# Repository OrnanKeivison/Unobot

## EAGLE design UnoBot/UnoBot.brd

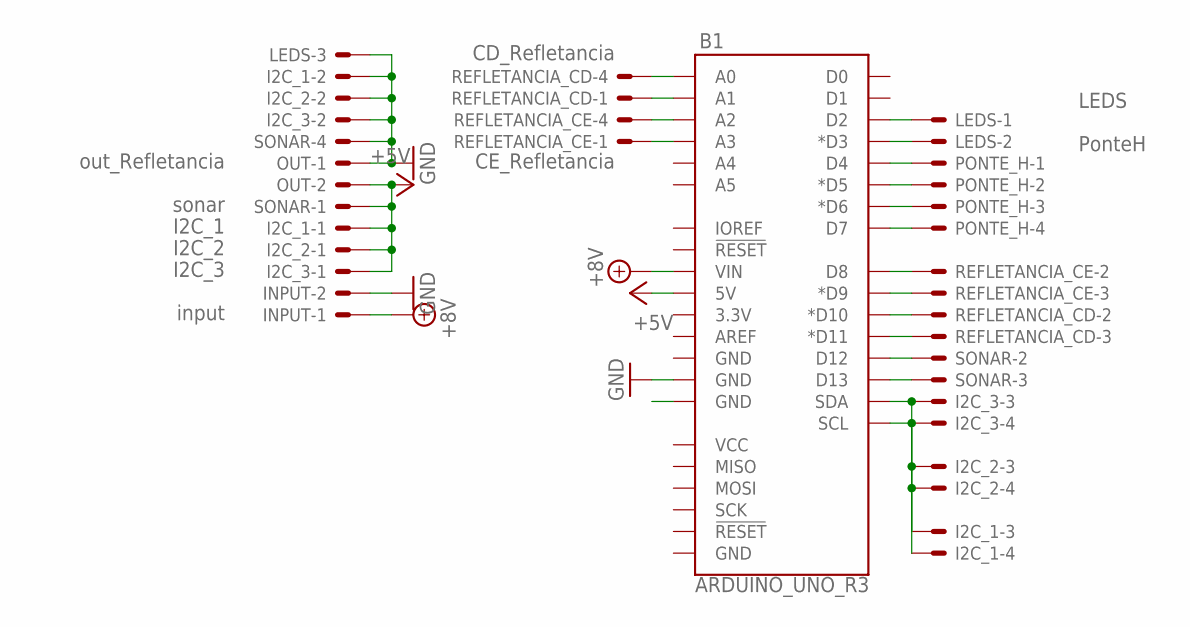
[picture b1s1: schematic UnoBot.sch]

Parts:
B1: ARDUINO_UNO_R3; ARDUINO_R3
I2C_1: I2C_1; JST-XH-04-PACKAGE-LONG-PAD
I2C_2: I2C_2; JST-XH-04-PACKAGE-LONG-PAD
I2C_3: I2C_3; JST-XH-04-PACKAGE-LONG-PAD
INPUT: input; JST-XH-02-PACKAGE-LONG-PAD
LEDS: LEDS; JST-XH-03-PACKAGE-LONG-PAD
OUT: out_Refletancia; JST-XH-02-PACKAGE-LONG-PAD
PONTE_H: PonteH; JST-XH-04-PACKAGE-LONG-PAD
REFLETANCIA_CD: CD_Refletancia; JST-XH-04-PACKAGE-LONG-PAD
REFLETANCIA_CE: CE_Refletancia; JST-XH-04-PACKAGE-LONG-PAD
SONAR: sonar; JST-XH-04-PACKAGE-LONG-PAD

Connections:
+5V: B1.5V, I2C_1.1, I2C_2.1, I2C_3.1, OUT.2, SONAR.1
+8V: B1.VIN, INPUT.1
GND: B1.GND@3 (GND), I2C_1.2, I2C_2.2, I2C_3.2, INPUT.2, LEDS.3, OUT.1, SONAR.4
unnamed: B1.D4, PONTE_H.1
unnamed: B1.D5 (*D5), PONTE_H.2
unnamed: B1.D6 (*D6), PONTE_H.3
unnamed: B1.D7, PONTE_H.4
unnamed: B1.A0, REFLETANCIA_CD.4
unnamed: B1.A1, REFLETANCIA_CD.1
unnamed: B1.A2, REFLETANCIA_CE.4
unnamed: B1.A3, REFLETANCIA_CE.1
unnamed: B1.D8, REFLETANCIA_CE.2
unnamed: B1.D9 (*D9), REFLETANCIA_CE.3
unnamed: B1.D10 (*D10), REFLETANCIA_CD.2
unnamed: B1.D11 (*D11), REFLETANCIA_CD.3
unnamed: B1.D13, SONAR.3
unnamed: B1.SDA, I2C_1.3, I2C_2.3, I2C_3.3
unnamed: B1.D12, SONAR.2
unnamed: B1.SCL, I2C_1.4, I2C_2.4, I2C_3.4
unnamed: B1.D2, LEDS.1
unnamed: B1.D3 (*D3), LEDS.2

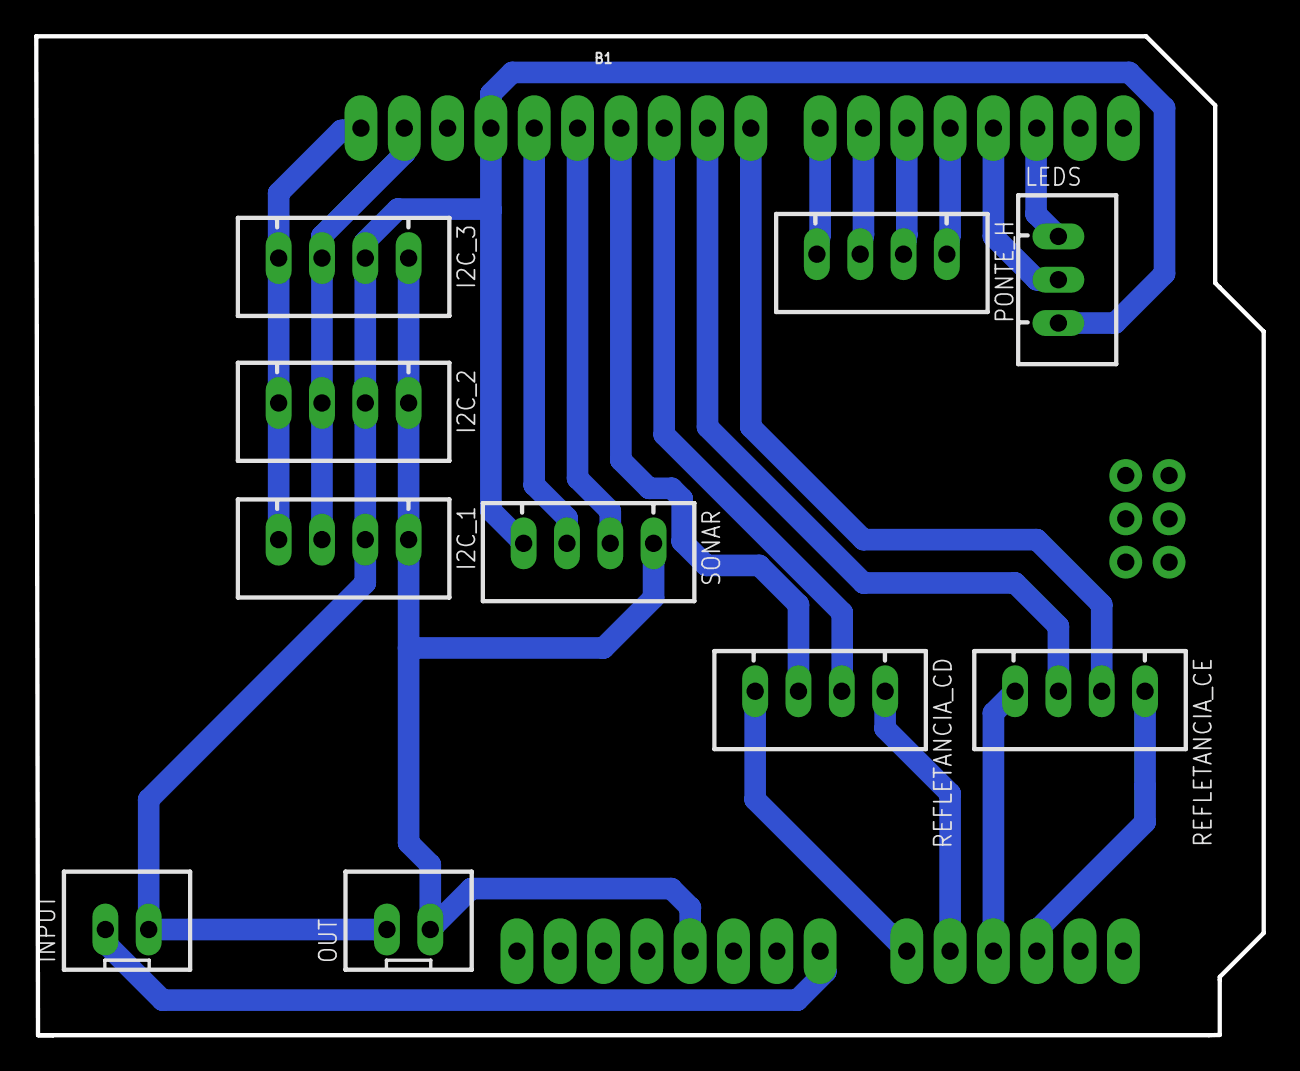
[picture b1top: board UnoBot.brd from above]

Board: 2 copper layers, 72.0 x 58.6 mm, 11 parts (0 on the bottom side), 21 nets.

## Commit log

2023-12-18 git add

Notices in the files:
parts and their libraries:
SparkFun-Boards: Licensing: Creative Commons ShareAlike 4.0 International - https://creativecommons.org/licenses/by-sa/4.0
